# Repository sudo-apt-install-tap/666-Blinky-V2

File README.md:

# 666-Blinky-V2

## Introduction
666-Blinky-V2 is a simple LED blinker PCB designed in KiCAD. It uses the 555 timer IC and an I/O expansion IC.

## Images

<br>

## Build Images

## Video Is On YouTube!

[Demo #004 V2](https://youtu.be/vR9sy3t7hsI)

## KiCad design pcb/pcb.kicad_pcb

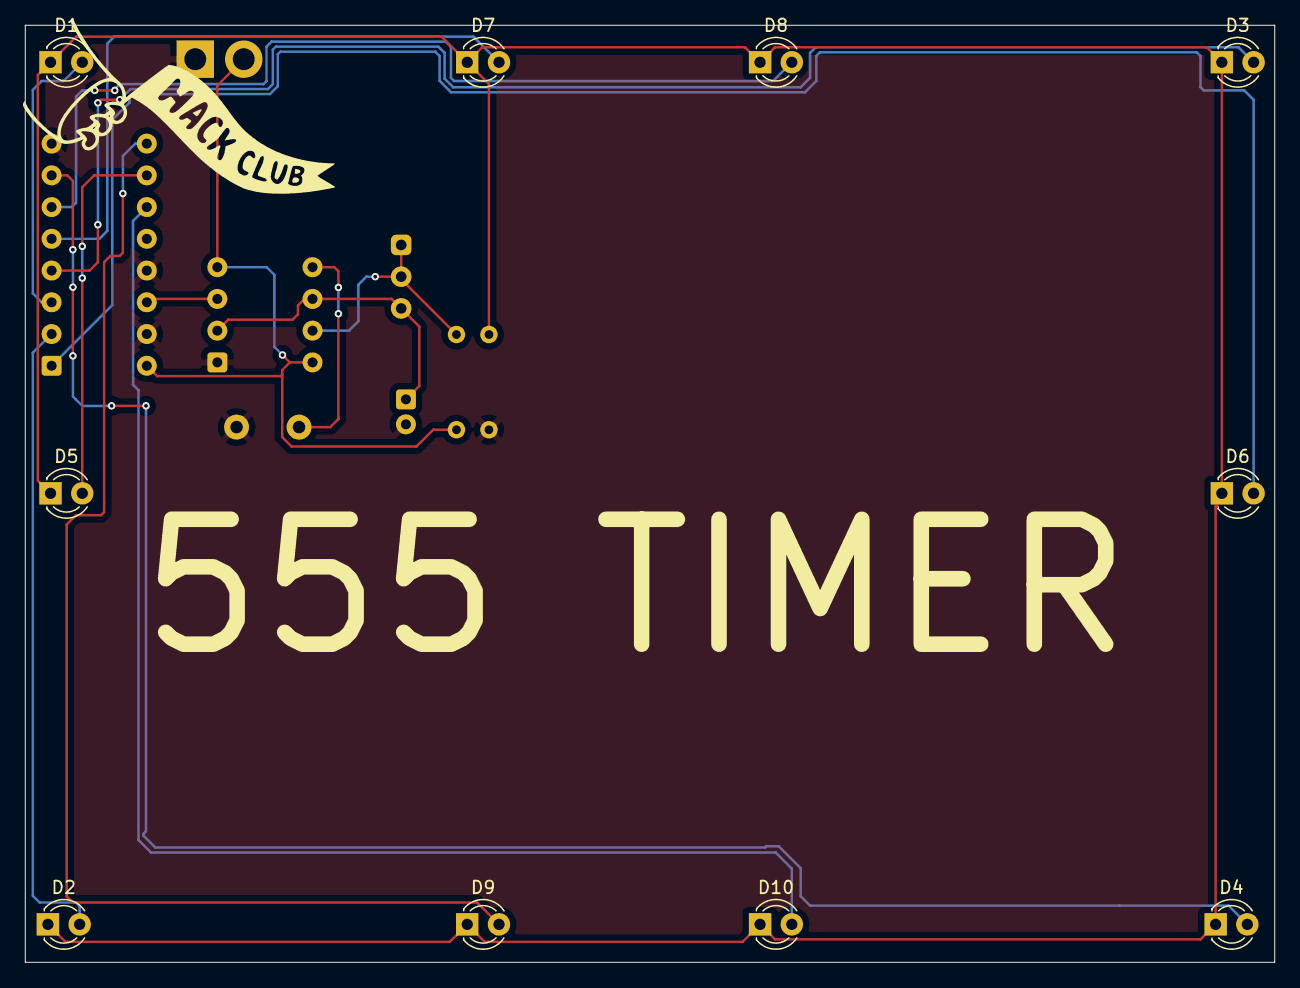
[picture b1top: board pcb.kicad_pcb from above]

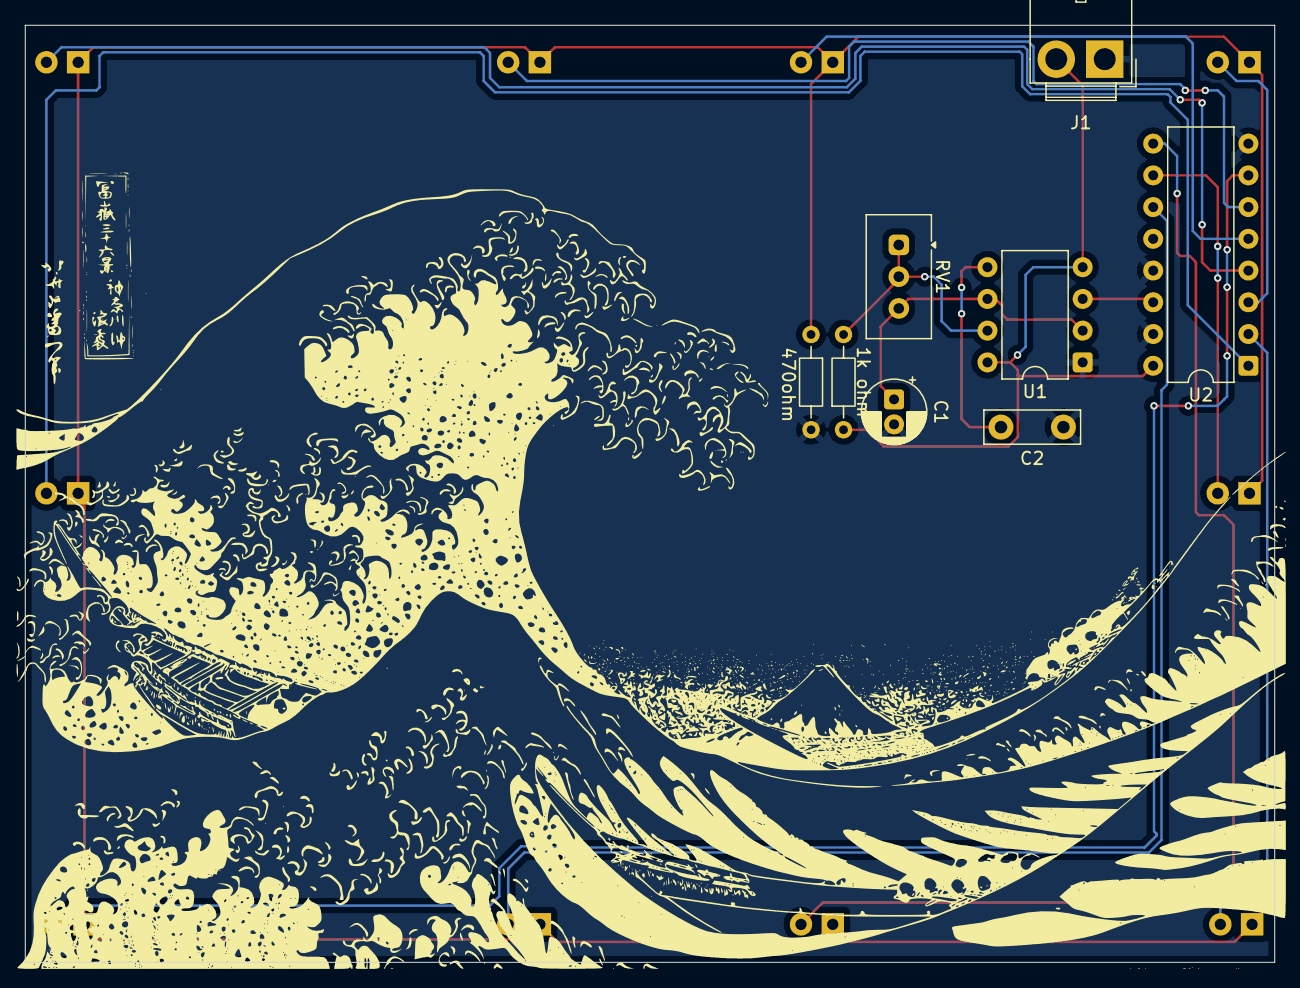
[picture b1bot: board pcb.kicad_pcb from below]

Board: 2 copper layers, 100.0 x 75.0 mm, 18 parts (8 on the bottom side), 17 nets.

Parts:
1k ohm: 470; R_Axial_DIN0204_L3.6mm_D1.6mm_P7.62mm_Horizontal
470ohm: 1k; R_Axial_DIN0204_L3.6mm_D1.6mm_P7.62mm_Horizontal
C1: 1uF; CP_Radial_D5.0mm_P2.00mm
C2: 0.01uf; C_Disc_D7.5mm_W2.5mm_P5.00mm
D1, D2, D3, D4, D5, D6, D7, D8, D9, D10: LED; LED_D3.0mm
J1: Conn_01x02_Pin; JWT_A3963_1x02_P3.96mm_Vertical
RV1: 5k; Potentiometer_Vishay_T93YA_Vertical
U1: NE555P; DIP-8_W7.62mm
U2: 4017; DIP-16_W7.62mm

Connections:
GND: 1k ohm.2, C1.2, C2.1, J1.1, U1.1 (GND), U2.8 (VSS), U2.13 (CKEN), U2.15 (Reset)
unnamed: D1.2 (A), U2.3 (Q0)
unnamed: 1k ohm.1, D1.1 (K), D2.1 (K), D3.1 (K), D4.1 (K), D5.1 (K), D6.1 (K), D7.1 (K), D8.1 (K), D9.1 (K), D10.1 (K)
unnamed: D2.2 (A), U2.2 (Q1)
unnamed: D3.2 (A), U2.4 (Q2)
unnamed: D4.2 (A), U2.7 (Q3)
unnamed: D5.2 (A), U2.10 (Q4)
unnamed: D6.2 (A), U2.1 (Q5)
unnamed: D7.2 (A), U2.5 (Q6)
unnamed: D8.2 (A), U2.6 (Q7)
unnamed: D9.2 (A), U2.9 (Q8)
unnamed: D10.2 (A), U2.11 (Q9)
unnamed: C2.2, U1.5 (CONT)
unnamed: 470ohm.2, RV1.1, RV1.2, U1.7 (DISCH)
OUT: U1.3 (OUT), U2.14 (CLK)
TR: C1.1, RV1.3, U1.2 (TRIG), U1.6 (THRES)
VCC: 470ohm.1, J1.2, U1.4 (~RST), U1.8 (VCC), U2.16 (VDD)

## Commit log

2026-03-11 Initialize README with project details and images
    Added project description and images to README.
2026-03-11 Added Gerbers
2026-03-11 Added Cart Images
